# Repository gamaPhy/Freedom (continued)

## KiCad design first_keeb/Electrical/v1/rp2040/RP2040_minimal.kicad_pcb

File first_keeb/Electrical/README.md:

## Electrical stuff

### TODO
- [ ] LEDs
  - [ ] Power with VSYS or VBUS?
  - [ ] Add addressable LED footprints to pcb
    - [ ] Choose suitable LEDs
- [ ] ADC
  - [ ] analog and digital ground plane placement
  - [ ] option to add external ADC
    - [ ] select suitable ICs
    - [ ] SPI or I2C?
    - [ ] Power with VSYS or VBUS?
    - [ ] option to use 3v3 or 5v to power? 
- [ ] HES (Hall effect sensors)
  - [ ] option to use 3v3 or 5v to power
  - [ ] What type of filter?
  - [ ] Power with VSYS or VBUS?
- [ ] Extra buttons for menu screen
- [ ] Add switch footprints to pcb
- [ ] Add extra switch with winding copper wire  around switch connected to ADC to test viability
- [ ] Rotary encoders with the internal ADC?

- SPI 
   - 0Ohm resistor terminations near source of  each line
- Debounce rotary encoder and buttons

Future:
- Find a suitable voltage regulator or voltage reference to accomodate powering all the sensors. 
  ~10mA maximum each * 16 = 160mA total. This might be too much load on 3v3 pin of pico.

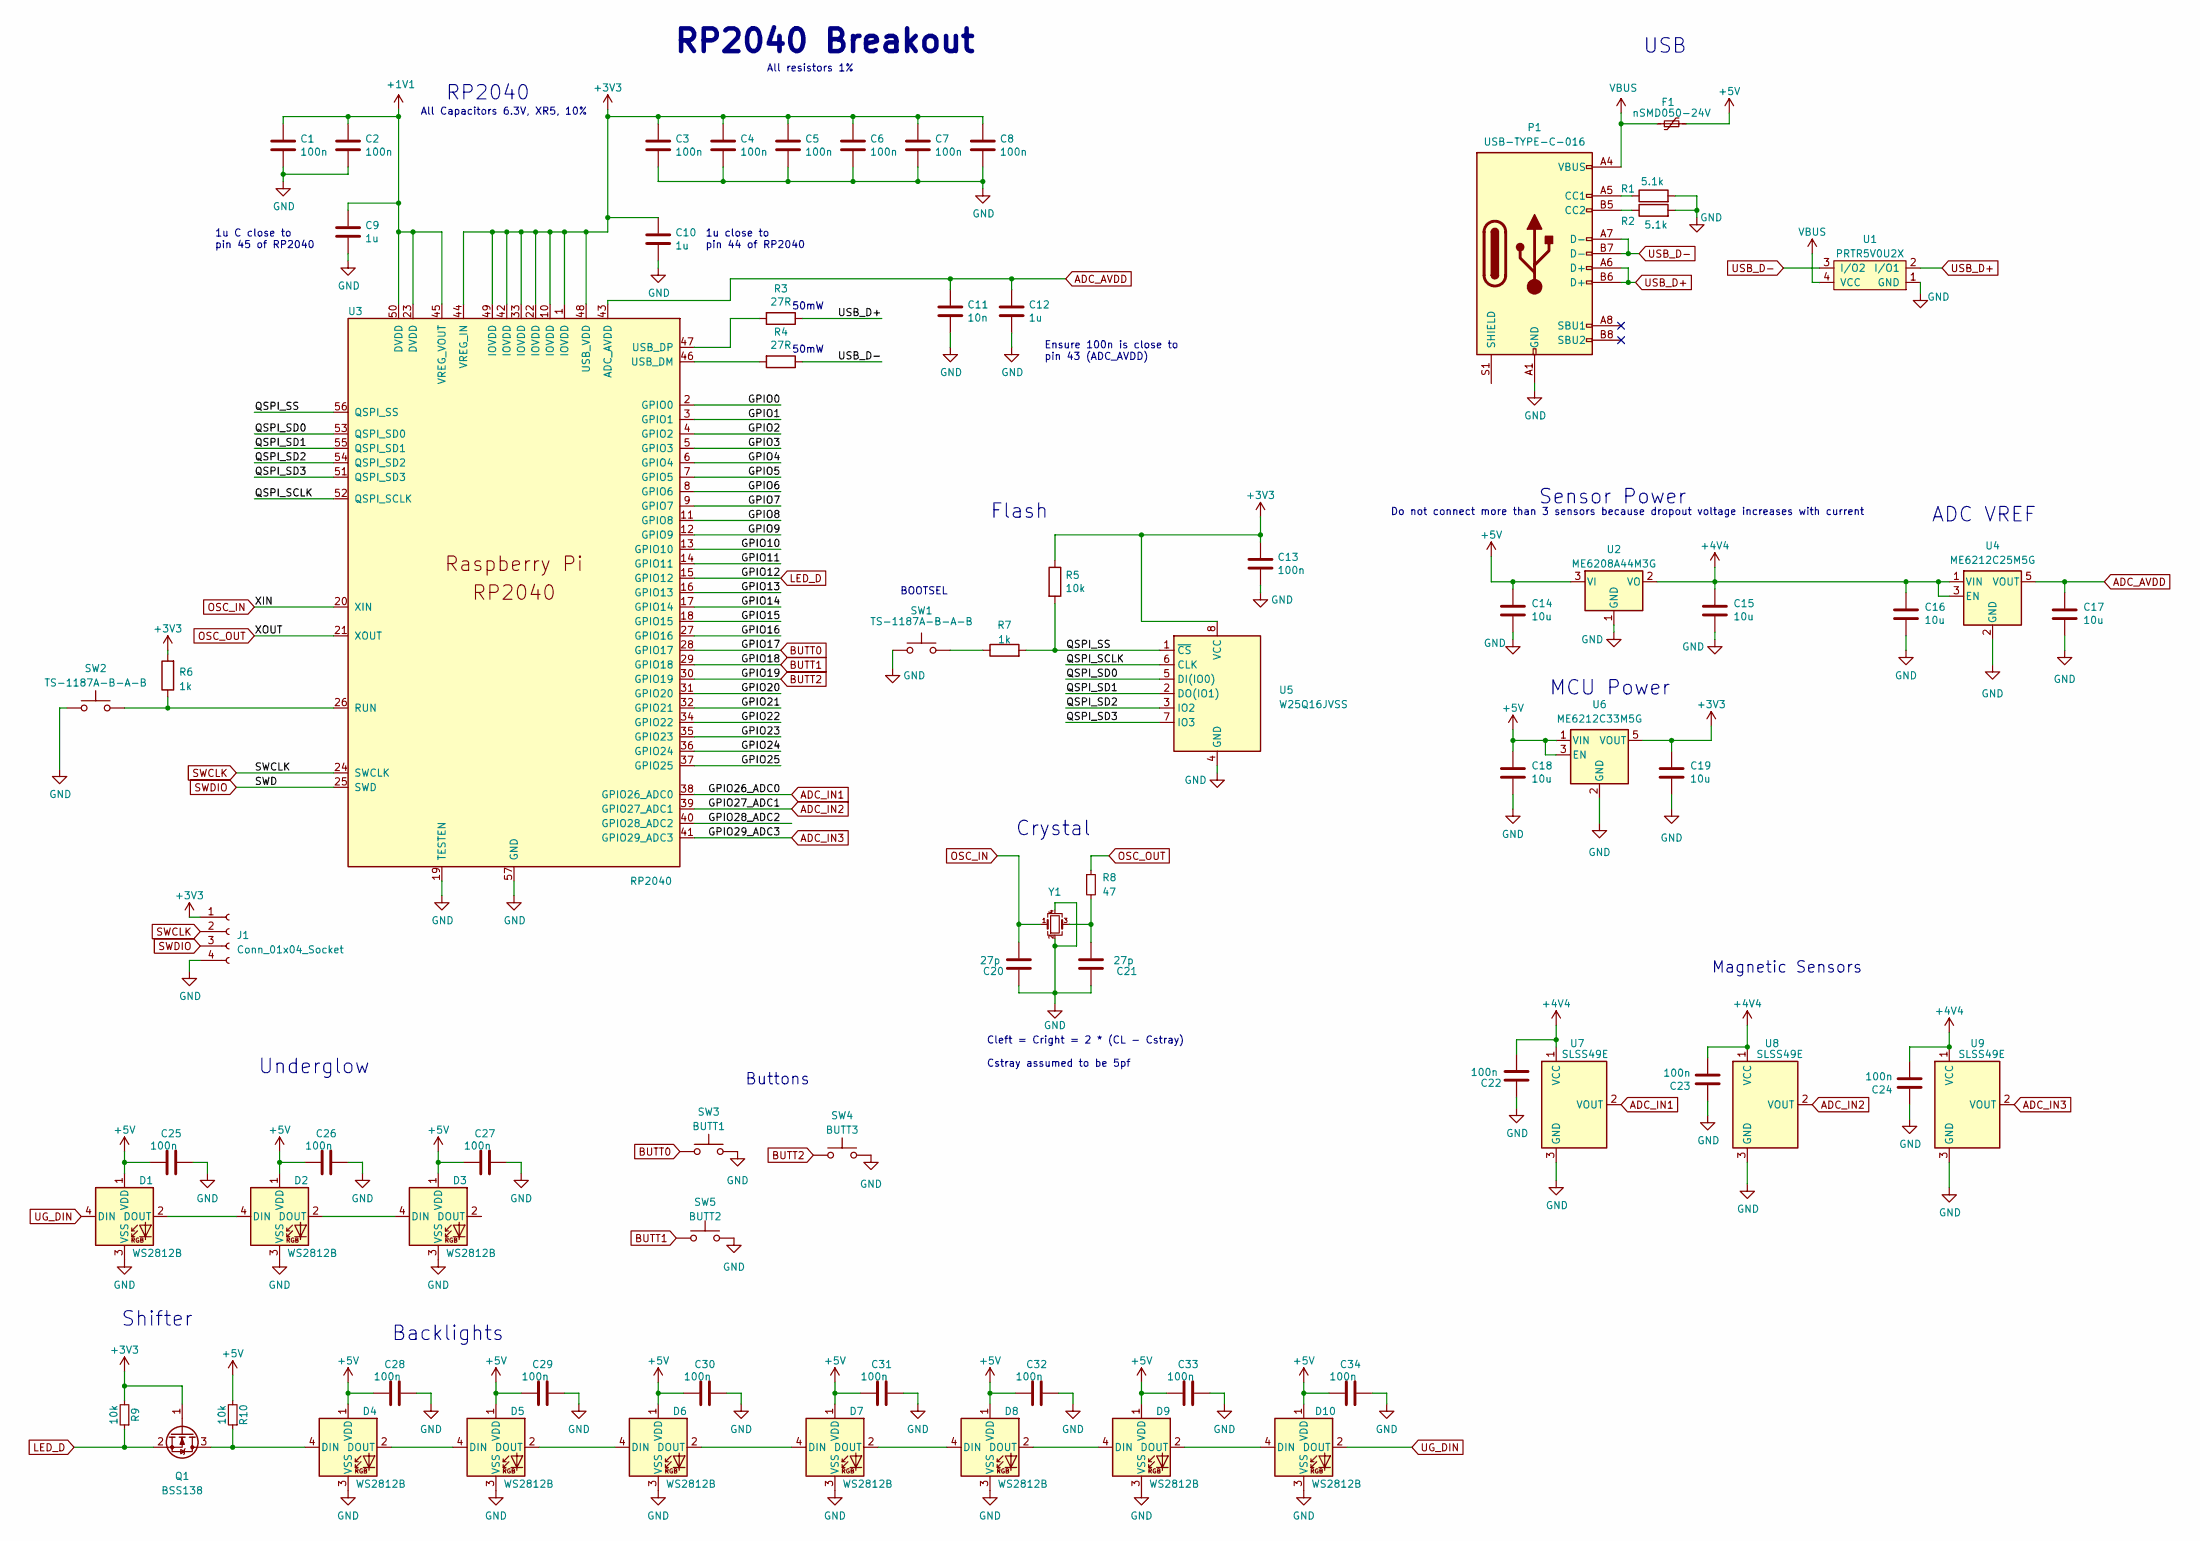
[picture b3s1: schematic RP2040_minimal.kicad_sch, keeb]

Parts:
C1, C2, C3, C4, C5, C6, C7, C8, C13, C22, C23, C24, C25, C26, C27, C28, C29, C30, C31, C32, C33, C34: 100n; C_0402_1005Metric
C9, C10, C12: 1u; C_0402_1005Metric
C11: 10n; C_0402_1005Metric
C14, C15, C16, C17, C18, C19: 10u; C_1206_3216Metric
C20, C21: 27p; C_0402_1005Metric
D1, D2, D3, D4, D5, D6, D7, D8, D9, D10: WS2812B; LED_WS2812B_PLCC4_5.0x5.0mm_P3.2mm
F1: nSMD050-24V; Fuse_1206_3216Metric
J1: Conn_01x04_Socket; PinSocket_1x04_P2.54mm_Vertical
P1: USB-TYPE-C-016; USB-TYPE-C-016_Receptacle_DEALON_16P_MidMnt
Q1: BSS138; SOT-23
R1, R2: 5.1k; C_0402_1005Metric
R3, R4: 27R; C_0402_1005Metric
R5: 10k; C_0402_1005Metric
R6, R7: 1k; C_0402_1005Metric
R8: 47; R_0402_1005Metric; LCSC Part # C25118
R9, R10: 10k; R_0402_1005Metric; LCSC Part # C25744
SW1, SW2: TS-1187A-B-A-B; TS-1187A
SW3: BUTT1; SW_Push_1P1T_NO_6x6mm_H9.5mm
SW4: BUTT3; SW_Push_1P1T_NO_6x6mm_H9.5mm
SW5: BUTT2; SW_Push_1P1T_NO_6x6mm_H9.5mm
U1: PRTR5V0U2X; SOT-143B
U2: ME6208A44M3G; SOT-23-3
U3: RP2040; RP2040-QFN-56
U4: ME6212C25M5G; SOT-23-5
U5: W25Q16JVSS; SOIC-8_5.23x5.23mm_P1.27mm
U6: ME6212C33M5G; SOT-23-5
U7, U8, U9: SLSS49E; SOT-23
Y1: 12MHz; Crystal_SMD_3225-4Pin_3.2x2.5mm; LCSC Part # C9002

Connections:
+1V1: C1.1, C2.1, C9.1, U3.23 (DVDD), U3.45 (VREG_VOUT), U3.50 (DVDD)
+3V3: C3.1, C4.1, C5.1, C6.1, C7.1, C8.1, C10.1, C13.1, C19.1, J1.1, Q1.1 (G), R5.1, R6.2, R9.2, U3.1 (IOVDD), U3.10 (IOVDD), U3.22 (IOVDD), U3.33 (IOVDD), U3.42 (IOVDD), U3.44 (VREG_IN), U3.48 (USB_VDD), U3.49 (IOVDD), U5.8 (VCC), U6.5 (VOUT)
+4V4: C15.1, C16.1, C22.2, C23.2, C24.2, U2.2 (VO), U4.1 (VIN), U4.3 (EN), U7.1 (VCC), U8.1 (VCC), U9.1 (VCC)
+5V: C14.1, C18.1, C25.1, C26.1, C27.1, C28.1, C29.1, C30.1, C31.1, C32.1, C33.1, C34.1, D1.1 (VDD), D2.1 (VDD), D3.1 (VDD), D4.1 (VDD), D5.1 (VDD), D6.1 (VDD), D7.1 (VDD), D8.1 (VDD), D9.1 (VDD), D10.1 (VDD), F1.2, R10.2, U2.3 (VI), U6.1 (VIN), U6.3 (EN)
/GPIO0: U3.2 (GPIO0)
/GPIO1: U3.3 (GPIO1)
/GPIO2: U3.4 (GPIO2)
/GPIO3: U3.5 (GPIO3)
/GPIO4: U3.6 (GPIO4)
/GPIO5: U3.7 (GPIO5)
/GPIO6: U3.8 (GPIO6)
/GPIO7: U3.9 (GPIO7)
/GPIO8: U3.11 (GPIO8)
/GPIO9: U3.12 (GPIO9)
/GPIO10: U3.13 (GPIO10)
/GPIO11: U3.14 (GPIO11)
/GPIO13: U3.16 (GPIO13)
/GPIO14: U3.17 (GPIO14)
/GPIO15: U3.18 (GPIO15)
/GPIO16: U3.27 (GPIO16)
/GPIO20: U3.31 (GPIO20)
/GPIO21: U3.32 (GPIO21)
/GPIO22: U3.34 (GPIO22)
/GPIO23: U3.35 (GPIO23)
/GPIO24: U3.36 (GPIO24)
/GPIO25: U3.37 (GPIO25)
/GPIO28_ADC2: U3.40 (GPIO28_ADC2)
/QSPI_SCLK: U3.52 (QSPI_SCLK), U5.6 (CLK)
/QSPI_SD0: U3.53 (QSPI_SD0), U5.5 (DI(IO0))
/QSPI_SD1: U3.55 (QSPI_SD1), U5.2 (DO(IO1))
/QSPI_SD2: U3.54 (QSPI_SD2), U5.3 (IO2)
/QSPI_SD3: U3.51 (QSPI_SD3), U5.7 (IO3)
/QSPI_SS: R5.2, R7.2, U3.56 (QSPI_SS), U5.1 (~CS)
ADC_AVDD: C11.1, C12.1, C17.1, U3.43 (ADC_AVDD), U4.5 (VOUT)
ADC_IN1: U3.38 (GPIO26_ADC0), U7.2 (VOUT)
ADC_IN2: U3.39 (GPIO27_ADC1), U8.2 (VOUT)
ADC_IN3: U3.41 (GPIO29_ADC3), U9.2 (VOUT)
BUTT0: SW3.1, U3.28 (GPIO17)
BUTT1: SW5.1, U3.29 (GPIO18)
BUTT2: SW4.1, U3.30 (GPIO19)
GND: C1.2, C2.2, C3.2, C4.2, C5.2, C6.2, C7.2, C8.2, C9.2, C10.2, C11.2, C12.2, C13.2, C14.2, C15.2, C16.2, C17.2, C18.2, C19.2, C20.1, C21.1, C22.1, C23.1, C24.1, C25.2, C26.2, C27.2, C28.2, C29.2, C30.2, C31.2, C32.2, C33.2, C34.2, D1.3 (VSS), D2.3 (VSS), D3.3 (VSS), D4.3 (VSS), D5.3 (VSS), D6.3 (VSS), D7.3 (VSS), D8.3 (VSS), D9.3 (VSS), D10.3 (VSS), J1.4, P1.A1 (GND), P1.A12 (GND), P1.B1 (GND), P1.B12 (GND), R1.2, R2.2, SW1.1, SW2.1, SW3.2, SW4.2, SW5.2, U1.1 (GND), U2.1 (GND), U3.19 (TESTEN), U3.57 (GND), U4.2 (GND), U5.4 (GND), U6.2 (GND), U7.3 (GND), U8.3 (GND), U9.3 (GND), Y1.2, Y1.4
LED_D: Q1.2 (S), R9.1, U3.15 (GPIO12)
unnamed: C21.2, R8.2, Y1.3
unnamed: D1.2 (DOUT), D2.4 (DIN)
unnamed: D2.2 (DOUT), D3.4 (DIN)
unnamed: D4.4 (DIN), Q1.3 (D), R10.1
unnamed: D4.2 (DOUT), D5.4 (DIN)
unnamed: D5.2 (DOUT), D6.4 (DIN)
unnamed: D6.2 (DOUT), D7.4 (DIN)
unnamed: D7.2 (DOUT), D8.4 (DIN)
unnamed: D8.2 (DOUT), D9.4 (DIN)
unnamed: D9.2 (DOUT), D10.4 (DIN)
unnamed: P1.A5 (CC1), R1.1
unnamed: P1.B5 (CC2), R2.1
unnamed: R7.1, SW1.2
unnamed: R6.1, SW2.2, U3.26 (RUN)
unnamed: R4.2, U3.46 (USB_DM)
unnamed: R3.2, U3.47 (USB_DP)
OSC_IN: C20.2, U3.20 (XIN), Y1.1
OSC_OUT: R8.1, U3.21 (XOUT)
SWCLK: J1.2, U3.24 (SWCLK)
SWDIO: J1.3, U3.25 (SWD)
UG_DIN: D1.4 (DIN), D10.2 (DOUT)
USB_D+: P1.A6 (D+), P1.B6 (D+), R3.1, U1.2 (I/O1)
USB_D-: P1.A7 (D-), P1.B7 (D-), R4.1, U1.3 (I/O2)
VBUS: F1.1, P1.A4 (VBUS), P1.A9 (VBUS), P1.B4 (VBUS), P1.B9 (VBUS), U1.4 (VCC)

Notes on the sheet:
Sensor Power
50mW
RP2040 Breakout
Do not connect more than 3 sensors because dropout voltage increases with current
Backlights
Crystal
ADC VREF
Magnetic Sensors
Underglow
All Capacitors 6.3V, XR5, 10%
USB
Flash
Ensure 100n is close to pin 43 (ADC_AVDD)
1u close to pin 44 of RP2040
1u C close to pin 45 of RP2040
All resistors 1%
MCU Power
Buttons
Shifter
RP2040
Cleft = Cright = 2 * (CL - Cstray) Cstray assumed to be 5pf
BOOTSEL

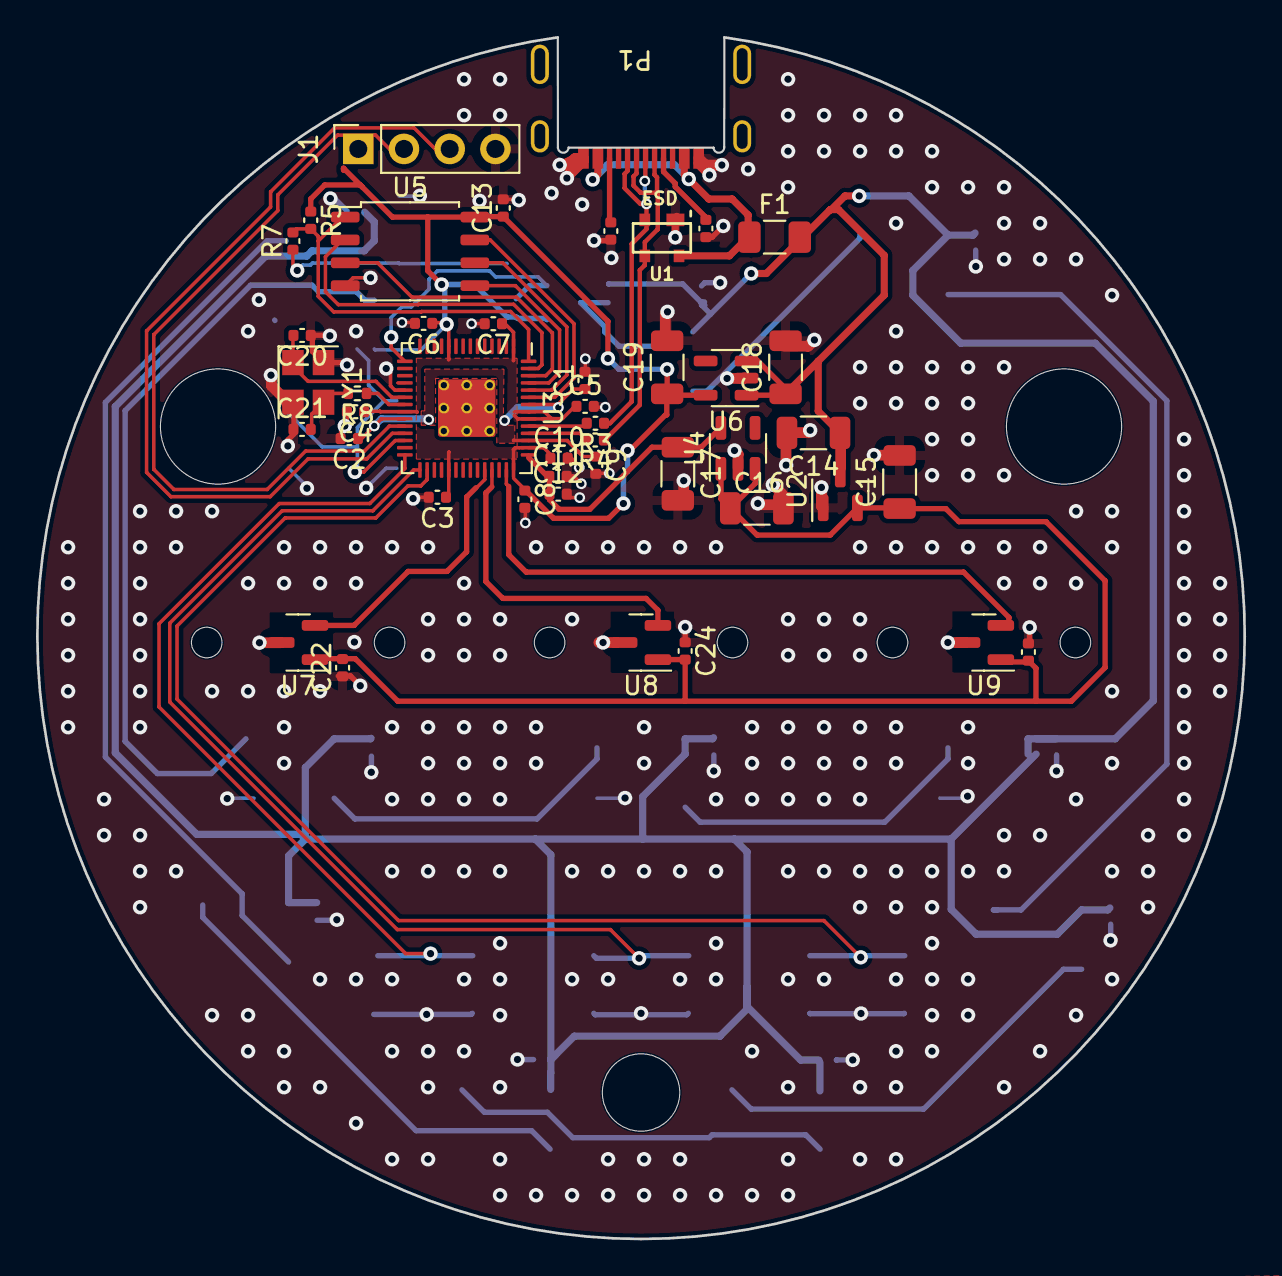
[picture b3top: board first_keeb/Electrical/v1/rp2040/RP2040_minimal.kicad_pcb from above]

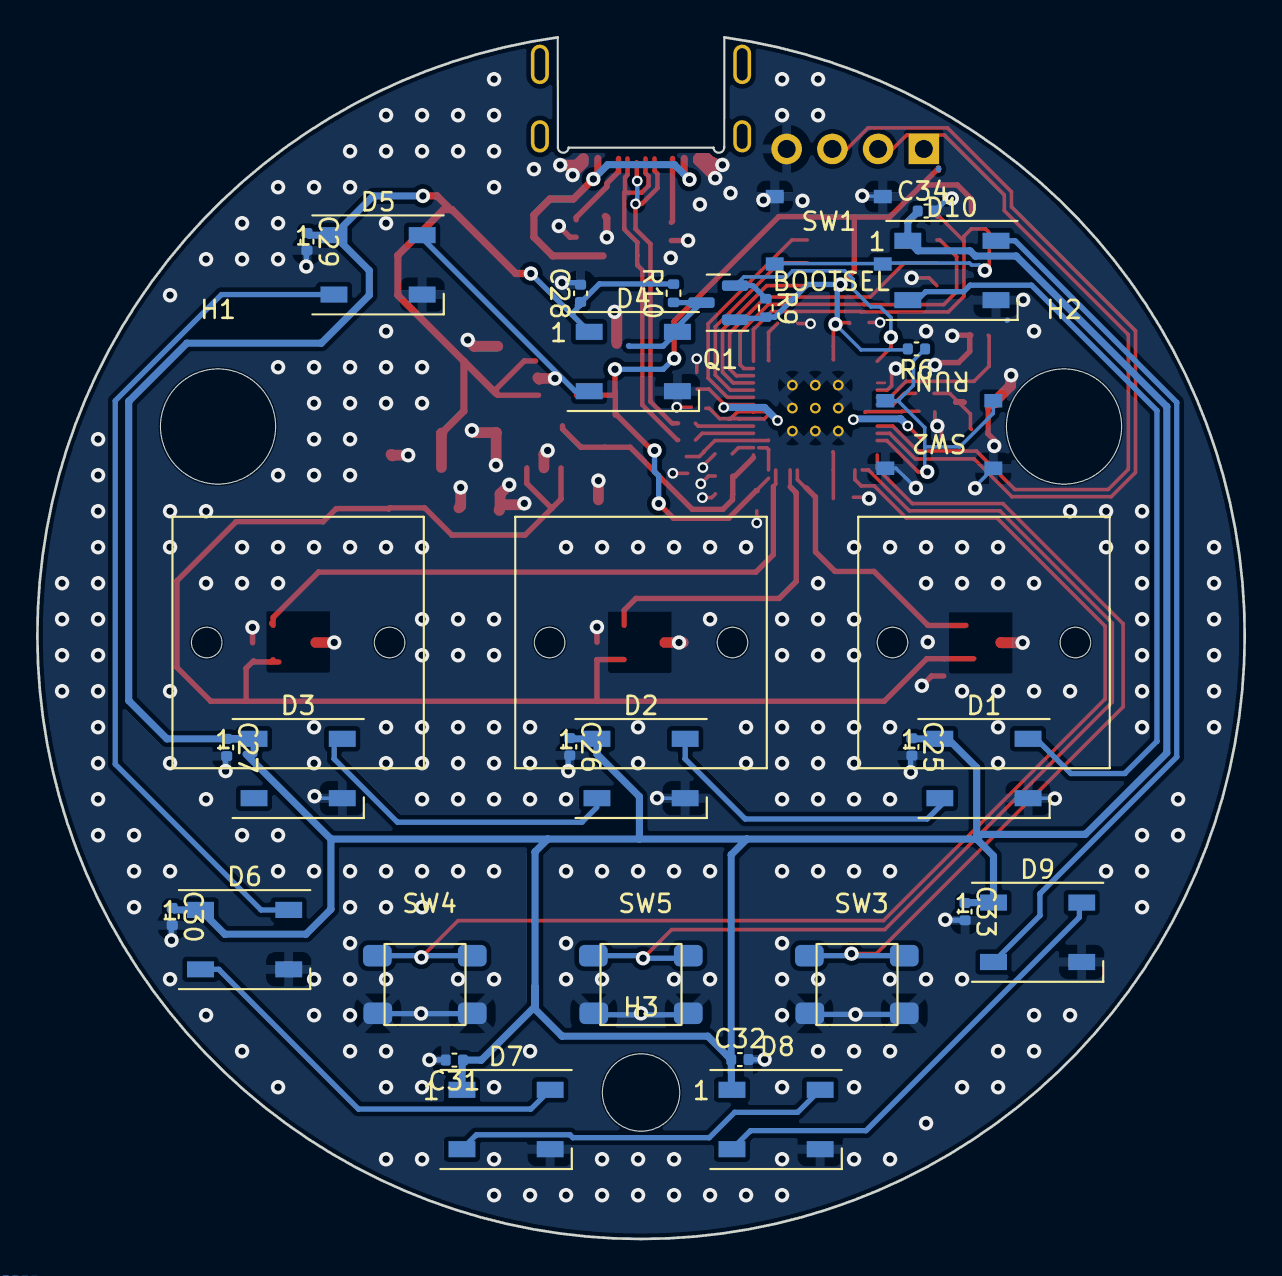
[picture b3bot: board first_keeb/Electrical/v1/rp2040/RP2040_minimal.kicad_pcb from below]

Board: 4 copper layers, 67.1 x 66.8 mm, 76 parts (32 on the bottom side), 43 nets.

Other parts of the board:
H1, H2: MountingHole_6.4mm_M6_DIN965
H3: MountingHole_4.3mm_M4_DIN965

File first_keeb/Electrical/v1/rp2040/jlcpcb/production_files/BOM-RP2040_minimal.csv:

Comment,Designator,Footprint,LCSC
100n,"C2,C3,C4,C5,C6",C_0402_1005Metric,C1525
47,R8,R_0402_1005Metric,C25118
10k,"R10,R9",R_0402_1005Metric,C25744
1u,C12,C_0402_1005Metric,C52923
12MHz,Y1,Crystal_SMD_3225-4Pin_3.2x2.5mm,C9002
10n,C11,C_0402_1005Metric,
100n,C8,C_0402_1005Metric,
PRTR5V0U2X,U1,SOT-143B,
10u,C17,C_1206_3216Metric,
100n,C7,C_0402_1005Metric,
1u,C10,C_0402_1005Metric,
10k,R5,C_0402_1005Metric,
100n,C1,C_0402_1005Metric,
W25Q16JVSS,U5,SOIC-8_5.23x5.23mm_P1.27mm,
10u,C16,C_1206_3216Metric,
10u,C15,C_1206_3216Metric,
BSS138,Q1,SOT-23,
5.1k,R1,C_0402_1005Metric,
RP2040,U3,RP2040-QFN-56,
ME6208A44M3G,U2,SOT-23,
5.1k,R2,C_0402_1005Metric,
10u,C14,C_1206_3216Metric,
10u,C18,C_1206_3216Metric,
1u,C9,C_0402_1005Metric,
100n,C13,C_0402_1005Metric,
27p,C20,C_0402_1005Metric,
27R,R3,C_0402_1005Metric,
10u,C19,C_1206_3216Metric,
USB-TYPE-C-016,P1,USB-TYPE-C-016_Receptacle_DEALON_16P_MidMnt,
nSMD050-24V,F1,Fuse_1206_3216Metric,
100n,C26,C_0402_1005Metric,
100n,C29,C_0402_1005Metric,
100n,C25,C_0402_1005Metric,
100n,C27,C_0402_1005Metric,
WS2812B,D2,LED_WS2812B_PLCC4_5.0x5.0mm_P3.2mm,
27p,C21,C_0402_1005Metric,
100n,C22,C_0402_1005Metric,
WS2812B,D5,LED_WS2812B_PLCC4_5.0x5.0mm_P3.2mm,
100n,C23,C_0402_1005Metric,
WS2812B,D7,LED_WS2812B_PLCC4_5.0x5.0mm_P3.2mm,
WS2812B,D3,LED_WS2812B_PLCC4_5.0x5.0mm_P3.2mm,
WS2812B,D9,LED_WS2812B_PLCC4_5.0x5.0mm_P3.2mm,
BUTT1,SW3,PTS647_4.5x4.5mm,
WS2812B,D1,LED_WS2812B_PLCC4_5.0x5.0mm_P3.2mm,
WS2812B,D6,LED_WS2812B_PLCC4_5.0x5.0mm_P3.2mm,
WS2812B,D8,LED_WS2812B_PLCC4_5.0x5.0mm_P3.2mm,
100n,C28,C_0402_1005Metric,
WS2812B,D4,LED_WS2812B_PLCC4_5.0x5.0mm_P3.2mm,
100n,C24,C_0402_1005Metric,
SLSS49E,U9,SOT-23,
SLSS49E,U8,SOT-23,
SLSS49E,U7,SOT-23,
Conn_01x04_Socket,J1,PinSocket_1x04_P2.54mm_Vertical,
BUTT2,SW5,PTS647_4.5x4.5mm,
27R,R4,C_0402_1005Metric,
1k,R6,C_0402_1005Metric,
1k,R7,C_0402_1005Metric,
ME6212C33M5G,U6,SOT-23-5,
ME6212C25M5G,U4,SOT-23-5,
BUTT3,SW4,PTS647_4.5x4.5mm,
WS2812B,D10,LED_WS2812B_PLCC4_5.0x5.0mm_P3.2mm,
TS-1187A-B-A-B,SW1,TS-1187A,
100n,C33,C_0402_1005Metric,
100n,C34,C_0402_1005Metric,
100n,C32,C_0402_1005Metric,
TS-1187A-B-A-B,SW2,TS-1187A,
100n,C30,C_0402_1005Metric,
100n,C31,C_0402_1005Metric,

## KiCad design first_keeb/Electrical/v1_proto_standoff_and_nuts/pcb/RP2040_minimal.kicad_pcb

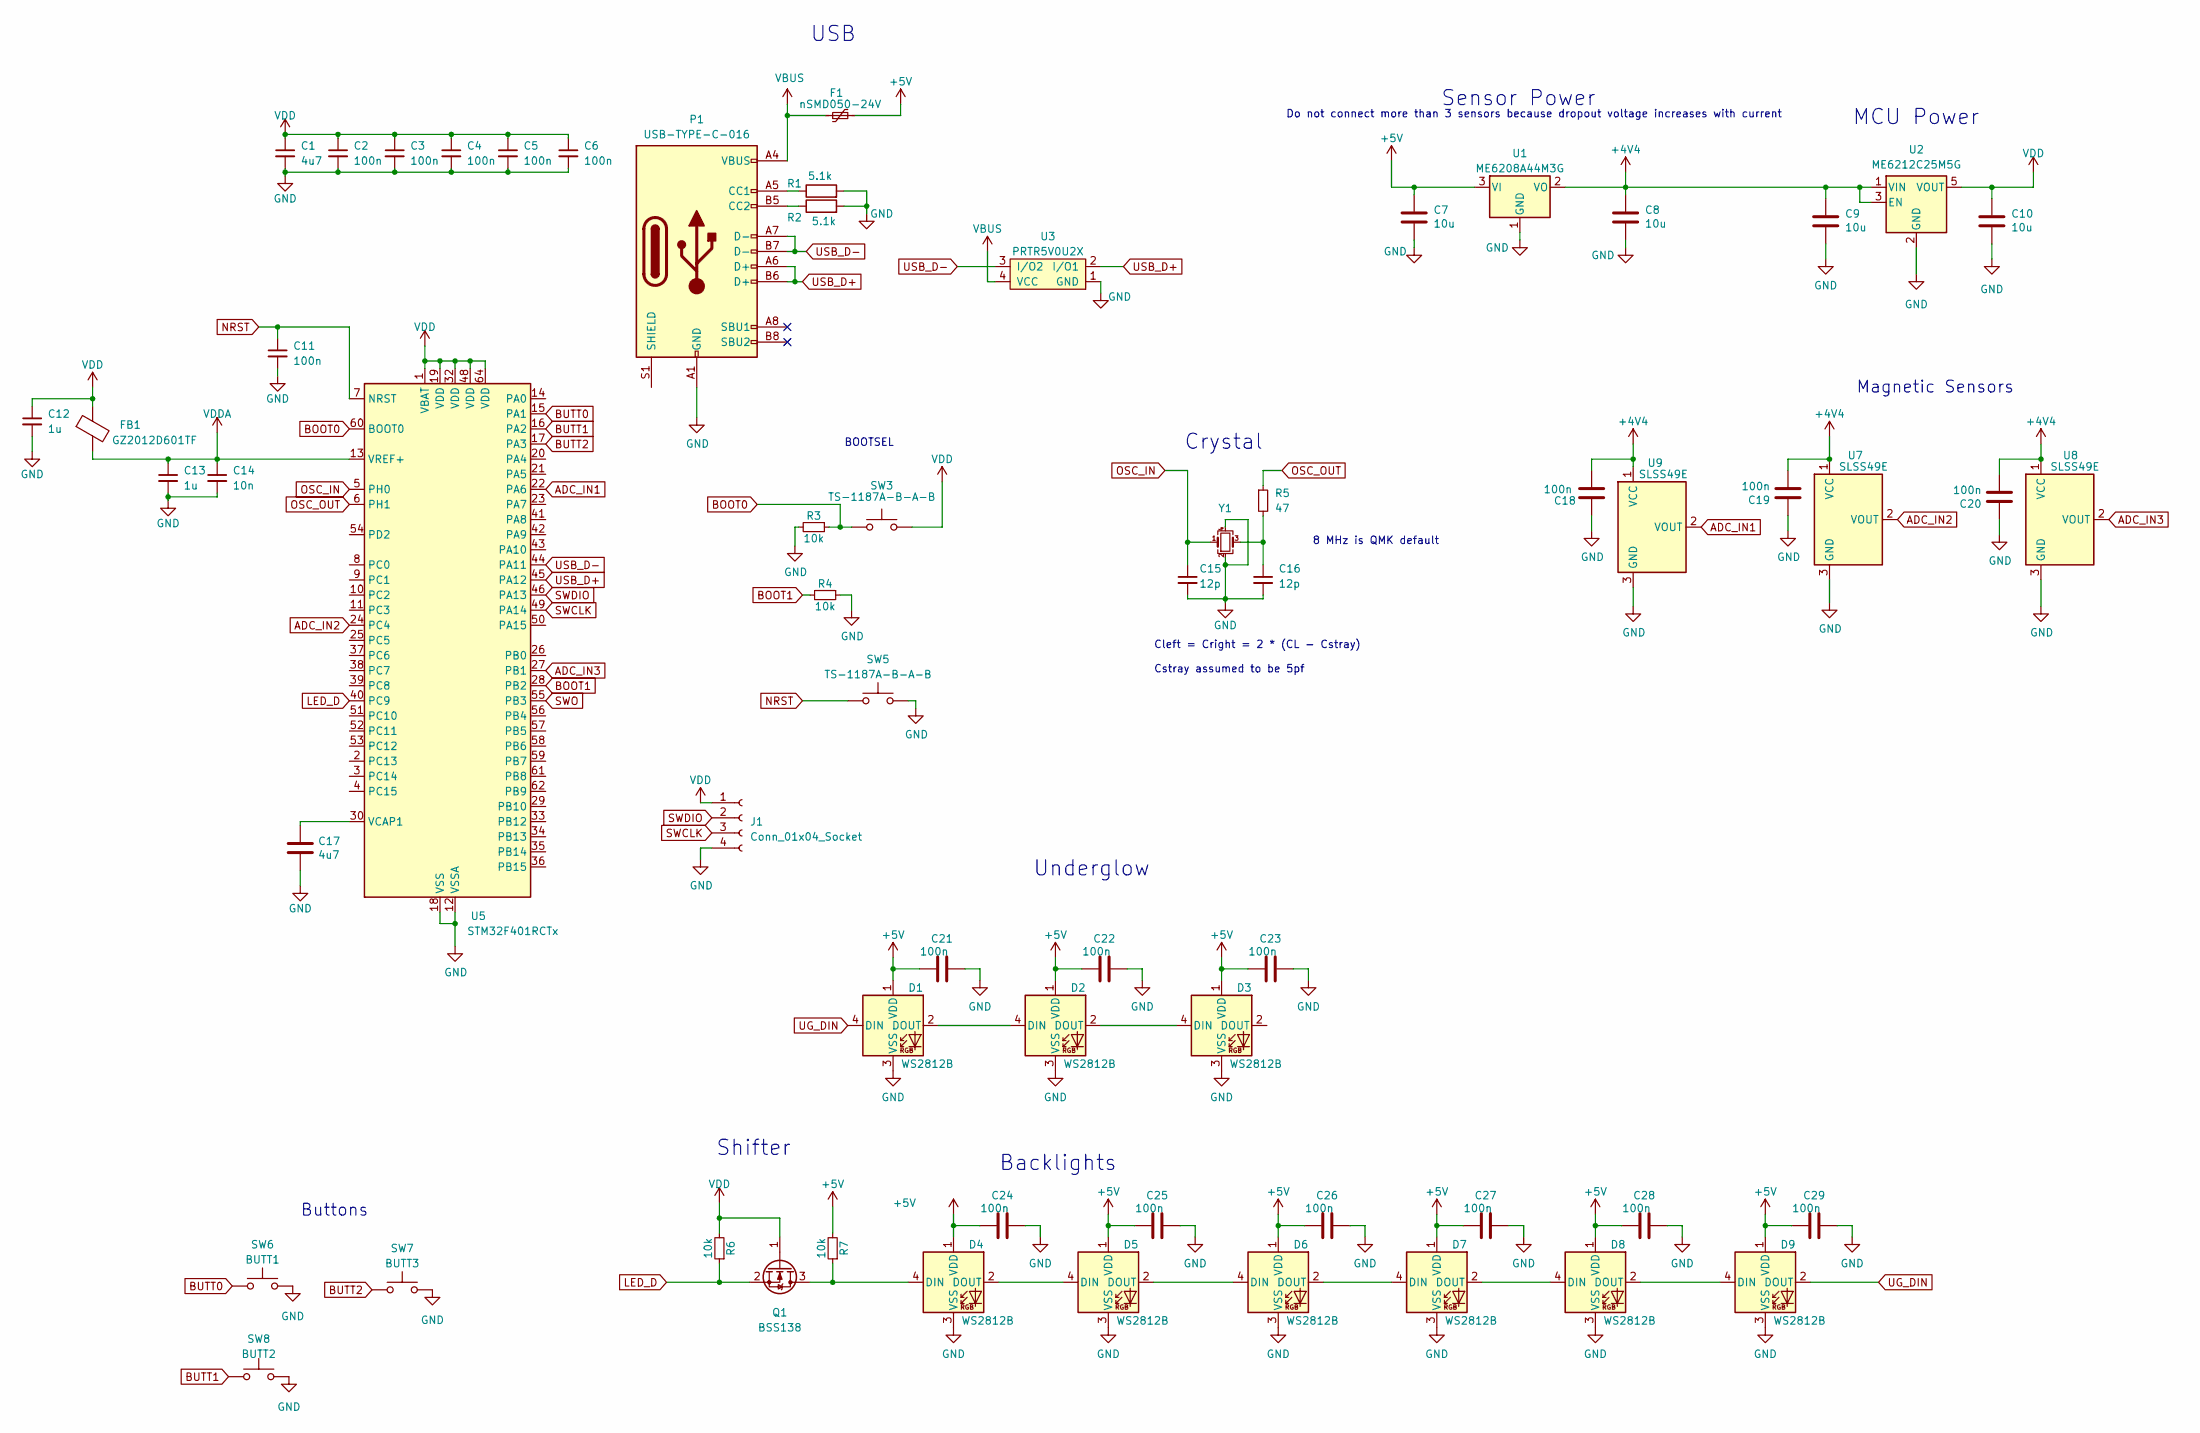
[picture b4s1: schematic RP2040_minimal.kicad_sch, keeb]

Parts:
C1: 4u7; C_0603_1608Metric; LCSC Part # C19666
C2, C3, C4, C5, C6, C11: 100n; C_0402_1005Metric; LCSC Part # C1525
C7, C8, C9, C10: 10u; C_1206_3216Metric
C12, C13: 1u; C_0402_1005Metric; LCSC Part # C52923
C14: 10n; C_0402_1005Metric; LCSC Part # C15195
C15, C16: 12p; C_0402_1005Metric; LCSC Part # C1547
C17: 4u7; C_0805_2012Metric
C18, C19, C20, C21, C22, C23, C24, C25, C26, C27, C28, C29: 100n; C_0402_1005Metric
D1, D2, D3, D4, D5, D6, D7, D8, D9: WS2812B; LED_WS2812B_PLCC4_5.0x5.0mm_P3.2mm
F1: nSMD050-24V; Fuse_1206_3216Metric
FB1: GZ2012D601TF; C_0805_2012Metric
J1: Conn_01x04_Socket; PinSocket_1x04_P2.54mm_Vertical
P1: USB-TYPE-C-016; USB-TYPE-C-016_Receptacle_DEALON_16P_MidMnt
Q1: BSS138; SOT-23
R1, R2: 5.1k; C_0402_1005Metric
R3, R4, R6, R7: 10k; R_0402_1005Metric; LCSC Part # C25744
R5: 47; R_0402_1005Metric; LCSC Part # C25118
SW3, SW5: TS-1187A-B-A-B; TS-1187A
SW6: BUTT1; SW_Push_1P1T_NO_6x6mm_H9.5mm
SW7: BUTT3; SW_Push_1P1T_NO_6x6mm_H9.5mm
SW8: BUTT2; SW_Push_1P1T_NO_6x6mm_H9.5mm
U1: ME6208A44M3G; SOT-23-3
U2: ME6212C25M5G; SOT-23-5
U3: PRTR5V0U2X; SOT-143B
U5: STM32F401RCTx; LQFP-64_10x10mm_P0.5mm
U7, U8, U9: SLSS49E; SOT-23
Y1: 8MHz; Crystal_SMD_3225-4Pin_3.2x2.5mm; LCSC Part # C13738

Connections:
+4V4: C8.1, C9.1, C18.2, C19.2, C20.2, U1.2 (VO), U2.1 (VIN), U2.3 (EN), U7.1 (VCC), U8.1 (VCC), U9.1 (VCC)
+5V: C7.1, C21.1, C22.1, C23.1, C24.1, C25.1, C26.1, C27.1, C28.1, C29.1, D1.1 (VDD), D2.1 (VDD), D3.1 (VDD), D4.1 (VDD), D5.1 (VDD), D6.1 (VDD), D7.1 (VDD), D8.1 (VDD), D9.1 (VDD), F1.2, R7.2, U1.3 (VI)
ADC_IN1: U5.22 (PA6), U9.2 (VOUT)
ADC_IN2: U5.24 (PC4), U7.2 (VOUT)
ADC_IN3: U5.27 (PB1), U8.2 (VOUT)
BOOT0: R3.1, SW3.1, U5.60 (BOOT0)
BOOT1: R4.2, U5.28 (PB2)
BUTT0: SW6.1, U5.15 (PA1)
BUTT1: SW8.1, U5.16 (PA2)
BUTT2: SW7.1, U5.17 (PA3)
GND: C1.2, C2.2, C3.2, C4.2, C5.2, C6.2, C7.2, C8.2, C9.2, C10.2, C11.2, C12.2, C13.2, C14.2, C15.2, C16.2, C17.2, C18.1, C19.1, C20.1, C21.2, C22.2, C23.2, C24.2, C25.2, C26.2, C27.2, C28.2, C29.2, D1.3 (VSS), D2.3 (VSS), D3.3 (VSS), D4.3 (VSS), D5.3 (VSS), D6.3 (VSS), D7.3 (VSS), D8.3 (VSS), D9.3 (VSS), J1.4, P1.A1 (GND), P1.A12 (GND), P1.B1 (GND), P1.B12 (GND), R1.2, R2.2, R3.2, R4.1, SW5.2, SW6.2, SW7.2, SW8.2, U1.1 (GND), U2.2 (GND), U3.1 (GND), U5.12 (VSSA), U5.18 (VSS), U5.31 (VSS), U5.47 (VSS), U5.63 (VSS), U7.3 (GND), U8.3 (GND), U9.3 (GND), Y1.2, Y1.4
LED_D: Q1.2 (S), R6.1, U5.40 (PC9)
NRST: C11.1, SW5.1, U5.7 (NRST)
unnamed: C16.1, R5.2, Y1.3
unnamed: D1.2 (DOUT), D2.4 (DIN)
unnamed: D2.2 (DOUT), D3.4 (DIN)
unnamed: D4.4 (DIN), Q1.3 (D), R7.1
unnamed: D4.2 (DOUT), D5.4 (DIN)
unnamed: D5.2 (DOUT), D6.4 (DIN)
unnamed: D6.2 (DOUT), D7.4 (DIN)
unnamed: D7.2 (DOUT), D8.4 (DIN)
unnamed: D8.2 (DOUT), D9.4 (DIN)
unnamed: P1.A5 (CC1), R1.1
unnamed: P1.B5 (CC2), R2.1
unnamed: C17.1, U5.30 (VCAP1)
OSC_IN: C15.1, U5.5 (PH0), Y1.1
OSC_OUT: R5.1, U5.6 (PH1)
SWCLK: J1.3, U5.49 (PA14)
SWDIO: J1.2, U5.46 (PA13)
SWO: U5.55 (PB3)
UG_DIN: D1.4 (DIN), D9.2 (DOUT)
USB_D+: P1.A6 (D+), P1.B6 (D+), U3.2 (I/O1), U5.45 (PA12)
USB_D-: P1.A7 (D-), P1.B7 (D-), U3.3 (I/O2), U5.44 (PA11)
VBUS: F1.1, P1.A4 (VBUS), P1.A9 (VBUS), P1.B4 (VBUS), P1.B9 (VBUS), U3.4 (VCC)
VDD: C1.1, C2.1, C3.1, C4.1, C5.1, C6.1, C10.1, C12.1, FB1.1, J1.1, Q1.1 (G), R6.2, SW3.2, U2.5 (VOUT), U5.1 (VBAT), U5.19 (VDD), U5.32 (VDD), U5.48 (VDD), U5.64 (VDD)
VDDA: C13.1, C14.1, FB1.2, U5.13 (VREF+)

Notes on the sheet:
Sensor Power
Do not connect more than 3 sensors because dropout voltage increases with current
BOOTSEL
8 MHz is QMK default
Backlights
Crystal
MCU Power
Magnetic Sensors
Underglow
USB
Buttons
Shifter
Cleft = Cright = 2 * (CL - Cstray) Cstray assumed to be 5pf

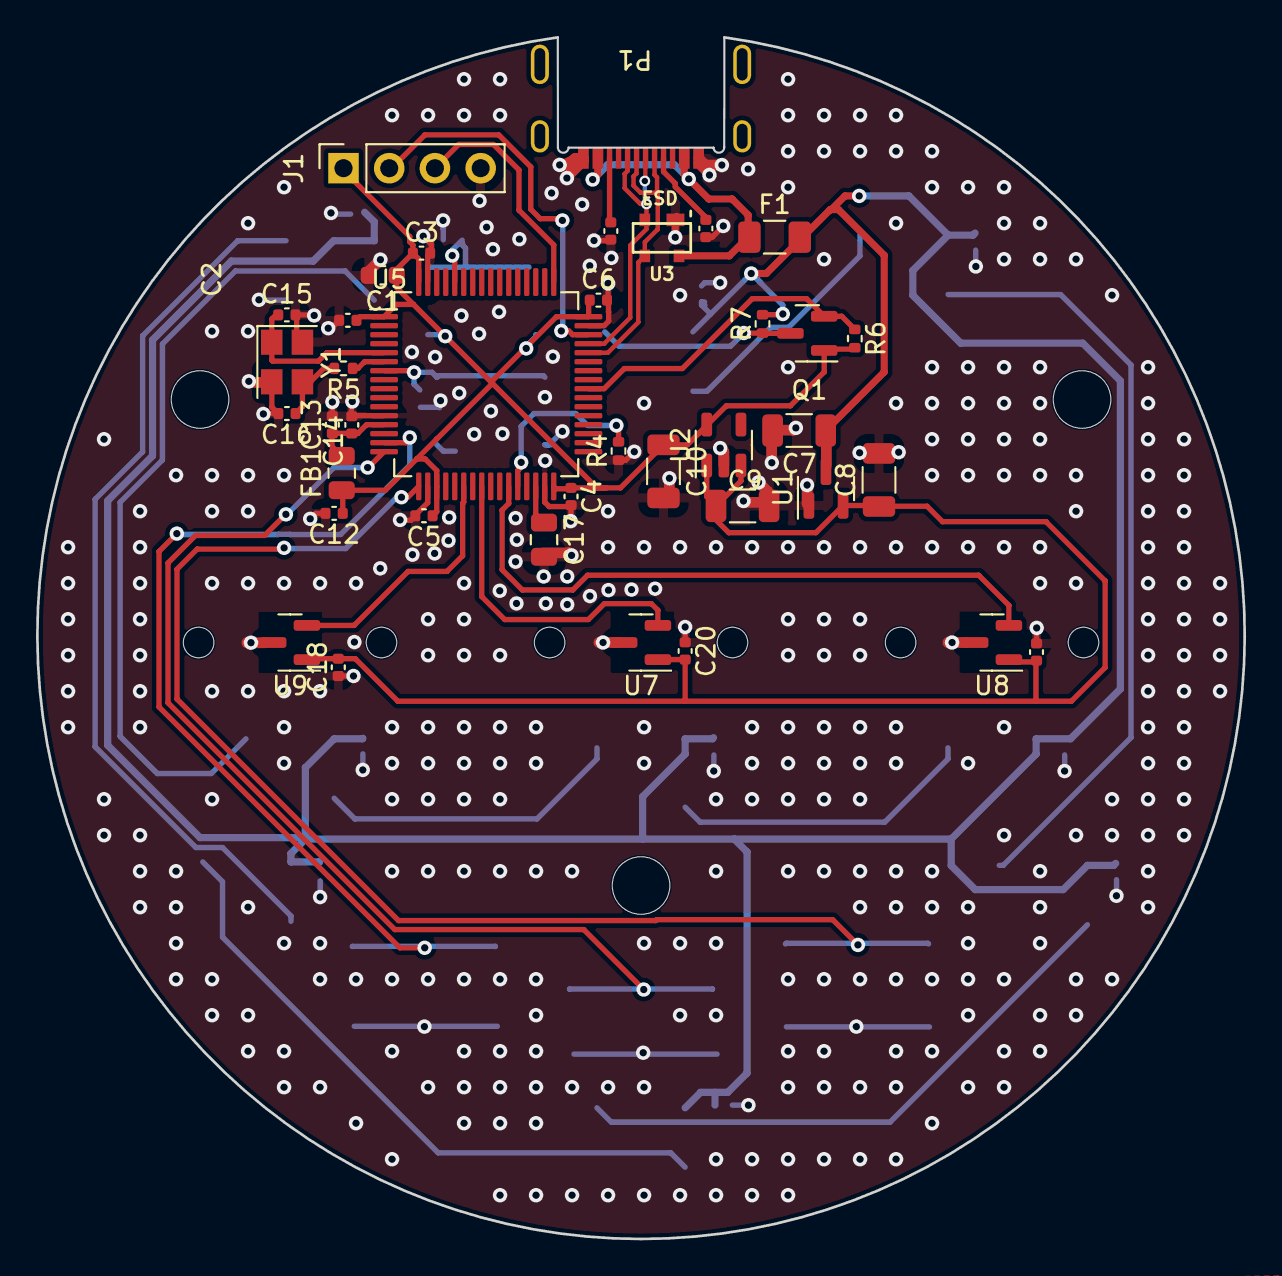
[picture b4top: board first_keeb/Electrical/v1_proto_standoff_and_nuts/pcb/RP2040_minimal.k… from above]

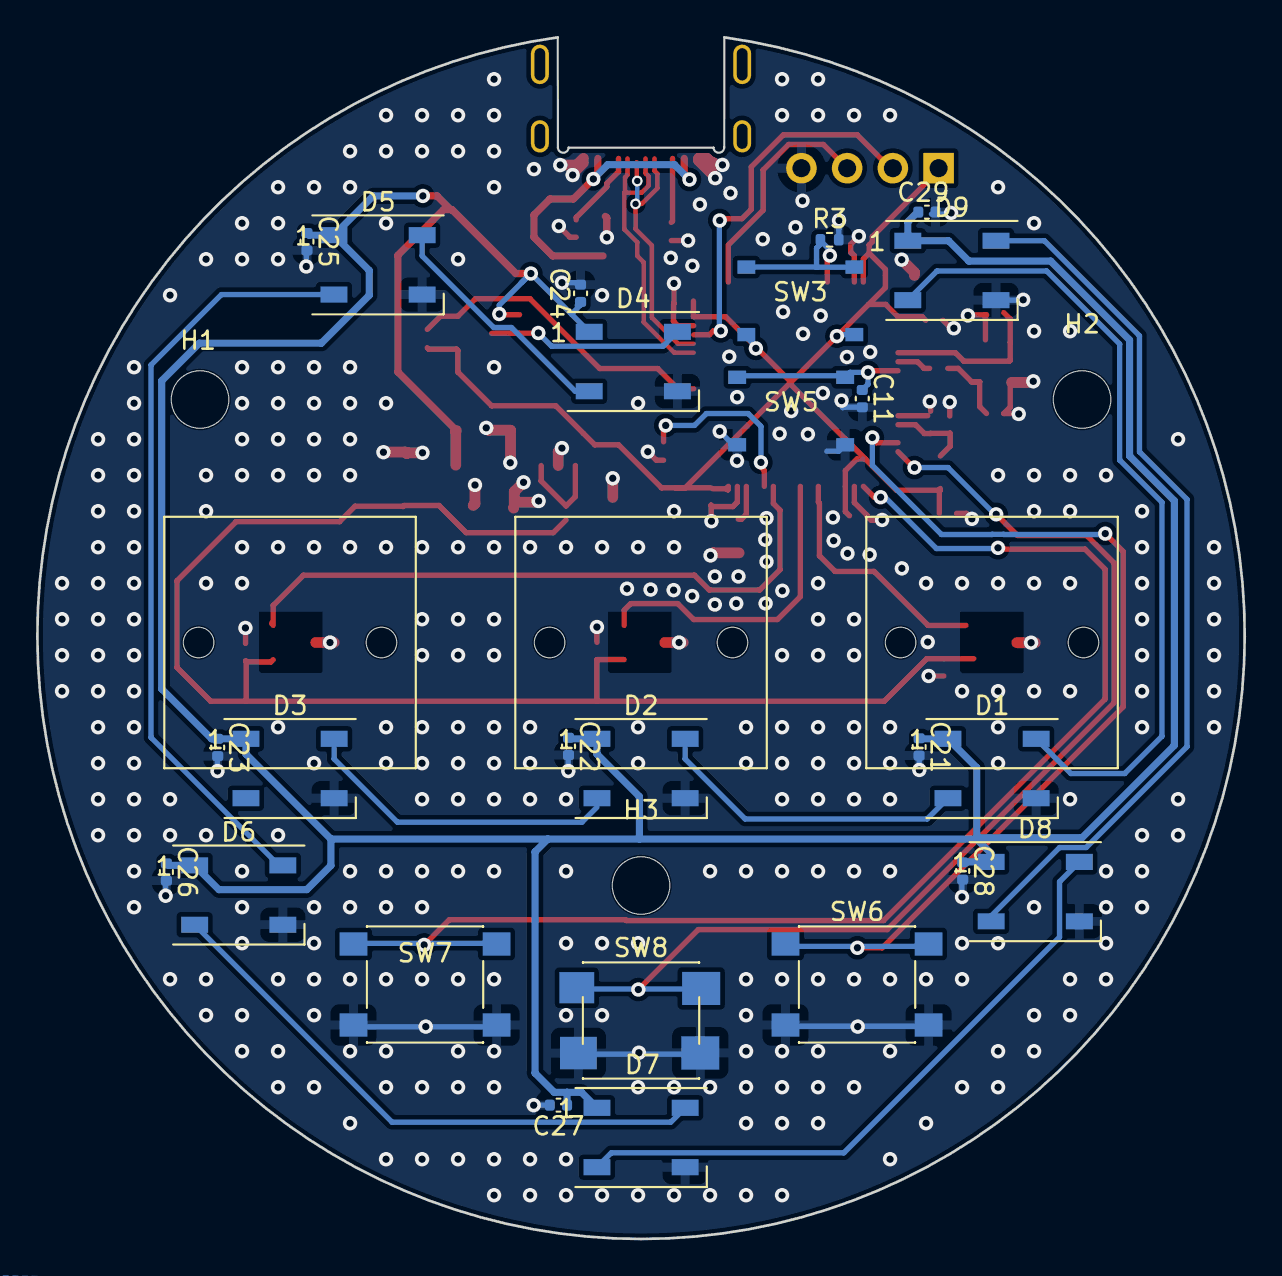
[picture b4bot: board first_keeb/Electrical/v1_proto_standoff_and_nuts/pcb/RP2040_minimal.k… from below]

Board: 4 copper layers, 67.1 x 66.8 mm, 66 parts (28 on the bottom side), 35 nets.

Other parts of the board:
H1, H2, H3: MountingHole_3.2mm_M3
